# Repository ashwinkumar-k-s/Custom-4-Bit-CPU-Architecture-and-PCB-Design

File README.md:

# Custom 4-Bit CPU Architecture and PCB Design

Designed and simulated a 4-bit microprocessor datapath using discrete logic, including an ALU, program counter, and memory units. Created full schematic and PCB layouts for all individual modules using KiCad, and successfully fabricated and tested the physical ALU board.

## System Architecture

This project implements a rudimentary discrete logic 4-bit processor datapath. The architecture is modularly designed, consisting of the following key components:

### Program Counter (PC)
* 2 Bit Counter using D-Flip Flop to cycle between 4 instructions

### Instruction Memory
* A network of 8 4x1 MUXs to obtain an instruction of 8 bit wide and have 4 instructions at a time loaded.

### 4x4 Memory Unit
* Consists of 4 2x4 Decoders, 4 4-Bit Registers and 4 4x1 MUXs.
* 2x4 Decoder : Used to load values into the register, controlled using Enable signals while in write mode.
* 4-Bit Register: Receives data from Decoders, interconnected as, all Bit-0s from decoder to Register-1, all Bit-1s from decoder to Register-2, all Bit-2s from decoder to Register-3, all Bit-3s from decoder to Register-4.
* 4x1 MUX: Used to read data from the register when in read mode, similar interconnect network as instruction memory.

### Operand controller
* Complementary pair of Tri-State Buffers connected to both Registers containing operand A and B

### Arithmetic Logic Unit (ALU)
* Could do 7 operations AND, OR, XOR, ADD, SUB, ROR, ROL.
* AND, OR, XOR operations are directly computed from the received inputs directly using dedicated ICs.
* ADD and SUB is done in a single circuit consisting of 2 Full adders and a XOR IC, where ADD = A+B and SUB = A + 2's complement(B).
* Rotate operations ROR (right) and ROL (left) is done with a 4-bit barrel shifter(used to shift in a single clock cycle).

### Output Control Unit
* All the outputs are simultaneouslly calculated in the ALU,
* Each output is 4-Bit wide and is connected to a dedicated set of 4-Bit Tri-state buffers controlled using a 3x8 Decoder to output the desired value.
  <br>

---

## Tools & Technologies

* **Logic Simulation:** Cedar Logic
* **Schematic Capture & PCB Layout:** KiCad
* **Hardware:** Discrete logic ICs, custom fabricated PCB

---

## Hardware Implementation & PCB Design

All functional modules were modeled, schematized, and routed as individual PCBs. The ALU module was fabricated in PCB and the rest were validated in breadboard circuitry.

### Hardware implementation of 4x4 Memory unit 

<br>

* 4 4x1 MUXs - 74LS153.
* 4 4-Bit Registers - 74LS173.
* 4 2x4 Decoder - 74LS139.
<br>

<br>

### Hardware implementation of Memory Data Register (Operand Selector)

<br>

* 3 4-Bit Registers - 74LS173.
* 1 8xTri-State Buffers - 74LS244.
* 1x2 Decoder made using AND and NOT ICs.

### ALU implementaion in PCB

<br>

* AND - 7408.
* OR - 7432.
* XOR - 7486.
* 4-Bit Full Adder - 7483.
* 4x1 MUX - 74153.
<br>

<br>

### Output Control Unit

<br>

* 3x8 Decoder - 74138.
* 7 4-Bit Registers - 74173.
<br>

<br>

### KiCad PCB Layouts

<br>

<br>

* PCB Layout of Memory Unit
<br>

<br>

<br>

* PCB layout of ALU
<br>

<br>

<br>

* PCB layout of Output Control Unit

### Cedar Logic Simulation

<br>

---

## Repository Structure

```text
├── simulations/          # Cedar Logic simulation files
│   ├── full_layout 
├── kicad_projects/       # KiCad schematics and PCB layout files
│   ├── Output_control_unit/
│   ├── ALU_module/
│   └── 4x4_Memory_Unit/     
└── README.md
 ```

## Contributors

This 4-bit CPU architecture and PCB design project was collaboratively developed as an assigned group project. 

* **[Adithya Balesh (CB.EN.U4ECE23005)/adithyabalesh]** - *Digital Design and Hardware Verification and PCB*
  * Instruction Memory and Component Integration and verification.
  * Hardware Implementation of Output control unit and ALU.
  * PCB routing and layout arrangement of memory.
  * Poster and Documentation.

* **[Ashwin Kumar K S (CB.EN.U4ECE23007)/ashwinkumar-k-s]** - *ALU Design and PCB routing,hardware impllementaion*
  * ALU, Output Control Unit and Datapath design.
  * Component Selection and Hardware implementation of ALU and Memory data register.
  * PCB routing, layout, and schematic generation of ALU and Output control Unit 
  * Documentation and Github Repo Creation.
  
* **[Chokkalingam S (CB.EN.U4ECE23012)/-------]** - *Memory Design and hardware impllementaion*
  * Digital design of 4x4 Memory Unit,  Memory Data Register Design and Pipeline/Interconnects accross all modules.
  * Hardware implementation and verification of Memory module and Instruction Memory.
  * PCB schematic of Memory module.
  * Documentation.

* **[Rohith J (CB.EN.U4ECE23017)/-------]** - *Digital Design and Hardware Verification*
  * Digital design verification of all components.
  * Hardware circuit implementation of and Memory Units.
  * PCB schematic verification and soldering.
  * Poster, Presentation and Documentation

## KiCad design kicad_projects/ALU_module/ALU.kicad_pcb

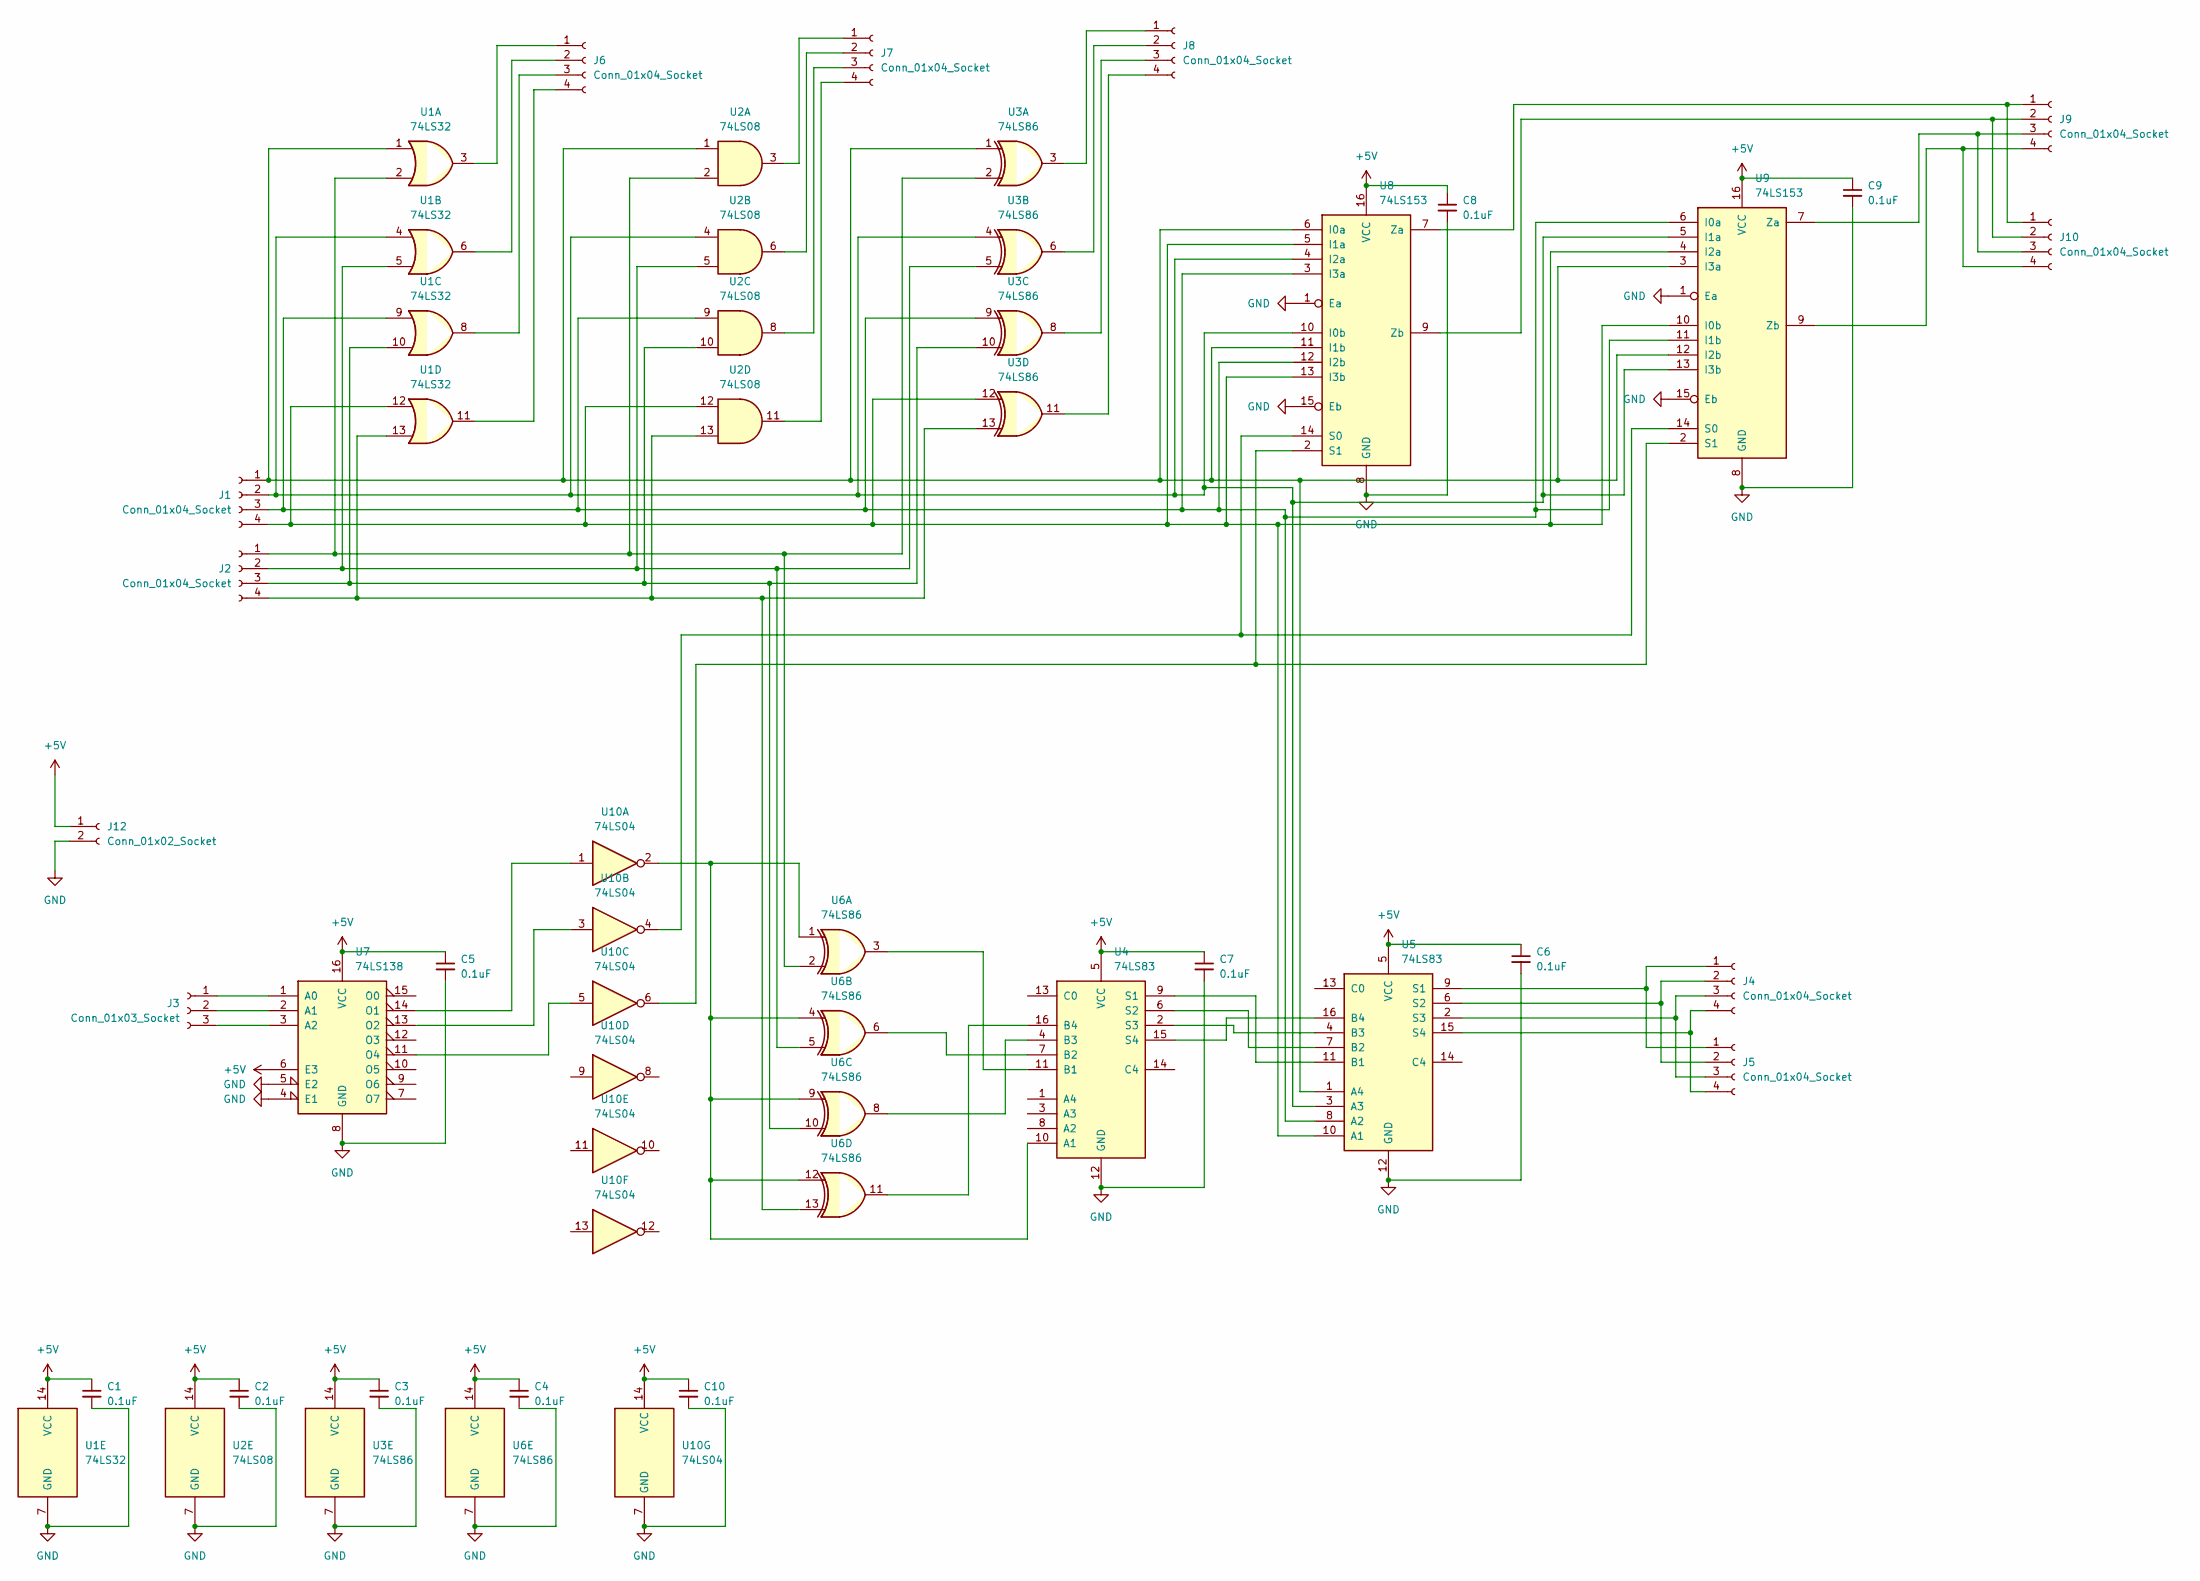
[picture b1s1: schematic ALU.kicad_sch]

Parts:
C1, C2, C3, C4, C5, C6, C7, C8, C9, C10: 0.1uF; C_Disc_D5.0mm_W2.5mm_P2.50mm
J1, J2, J4, J5, J6, J7, J8, J9, J10: Conn_01x04_Socket; PinSocket_1x04_P2.54mm_Vertical
J3: Conn_01x03_Socket; PinSocket_1x03_P2.54mm_Vertical
J12: Conn_01x02_Socket; PinSocket_1x02_P2.54mm_Vertical
U1: 74LS32; DIP-14_W7.62mm_LongPads
U2: 74LS08; DIP-14_W7.62mm_LongPads
U3, U6: 74LS86; DIP-14_W7.62mm_LongPads
U4, U5: 74LS83; DIP-16_W7.62mm_LongPads
U7: 74LS138; DIP-16_W7.62mm_LongPads
U8, U9: 74LS153; DIP-16_W7.62mm_LongPads
U10: 74LS04; DIP-14_W7.62mm_LongPads

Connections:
+5V: C1.1, C2.1, C3.1, C4.1, C5.1, C6.1, C7.1, C8.1, C9.1, C10.1, J12.1, U1.14 (VCC), U2.14 (VCC), U3.14 (VCC), U4.5 (VCC), U5.5 (VCC), U6.14 (VCC), U7.6 (E3), U7.16 (VCC), U8.16 (VCC), U9.16 (VCC), U10.14 (VCC)
GND: C1.2, C2.2, C3.2, C4.2, C5.2, C6.2, C7.2, C8.2, C9.2, C10.2, J12.2, U1.7 (GND), U2.7 (GND), U3.7 (GND), U4.12 (GND), U5.12 (GND), U6.7 (GND), U7.4 (E1), U7.5 (E2), U7.8 (GND), U8.1 (Ea), U8.8 (GND), U8.15 (Eb), U9.1 (Ea), U9.8 (GND), U9.15 (Eb), U10.7 (GND)
unnamed: J1.1, U1.1, U2.1, U3.1, U5.1 (A4), U8.6 (I0a), U8.11 (I1b), U9.3 (I3a), U9.12 (I2b)
unnamed: J1.2, U1.4, U2.4, U3.4, U5.3 (A3), U8.4 (I2a), U8.10 (I0b), U9.5 (I1a), U9.13 (I3b)
unnamed: J1.3, U1.9, U2.9, U3.9, U5.8 (A2), U8.3 (I3a), U8.12 (I2b), U9.6 (I0a), U9.11 (I1b)
unnamed: J1.4, U1.12, U2.12, U3.12, U5.10 (A1), U8.5 (I1a), U8.13 (I3b), U9.4 (I2a), U9.10 (I0b)
unnamed: J2.1, U1.2, U2.2, U3.2, U6.2
unnamed: J2.2, U1.5, U2.5, U3.5, U6.5
unnamed: J2.3, U1.10, U2.10, U3.10, U6.10
unnamed: J2.4, U1.13, U2.13, U3.13, U6.13
unnamed: J3.1, U7.1 (A0)
unnamed: J3.2, U7.2 (A1)
unnamed: J3.3, U7.3 (A2)
unnamed: J4.1, J5.1, U5.9 (S1)
unnamed: J4.2, J5.2, U5.6 (S2)
unnamed: J4.3, J5.3, U5.2 (S3)
unnamed: J4.4, J5.4, U5.15 (S4)
unnamed: J6.1, U1.3
unnamed: J6.2, U1.6
unnamed: J6.3, U1.8
unnamed: J6.4, U1.11
unnamed: J7.1, U2.3
unnamed: J7.2, U2.6
unnamed: J7.3, U2.8
unnamed: J7.4, U2.11
unnamed: J8.1, U3.3
unnamed: J8.2, U3.6
unnamed: J8.3, U3.8
unnamed: J8.4, U3.11
unnamed: J9.1, J10.1, U8.7 (Za)
unnamed: J9.2, J10.2, U8.9 (Zb)
unnamed: J9.3, J10.3, U9.7 (Za)
unnamed: J9.4, J10.4, U9.9 (Zb)
unnamed: U4.10 (A1), U6.1, U6.4, U6.9, U6.12, U10.2
unnamed: U4.11 (B1), U6.3
unnamed: U4.7 (B2), U6.6
unnamed: U4.4 (B3), U6.8
unnamed: U4.16 (B4), U6.11
unnamed: U4.9 (S1), U5.11 (B1)
unnamed: U4.6 (S2), U5.7 (B2)
unnamed: U4.2 (S3), U5.4 (B3)
unnamed: U4.15 (S4), U5.16 (B4)
unnamed: U7.14 (O1), U10.1
unnamed: U7.13 (O2), U10.3
unnamed: U7.11 (O4), U10.5
unnamed: U8.14 (S0), U9.14 (S0), U10.4
unnamed: U8.2 (S1), U9.2 (S1), U10.6

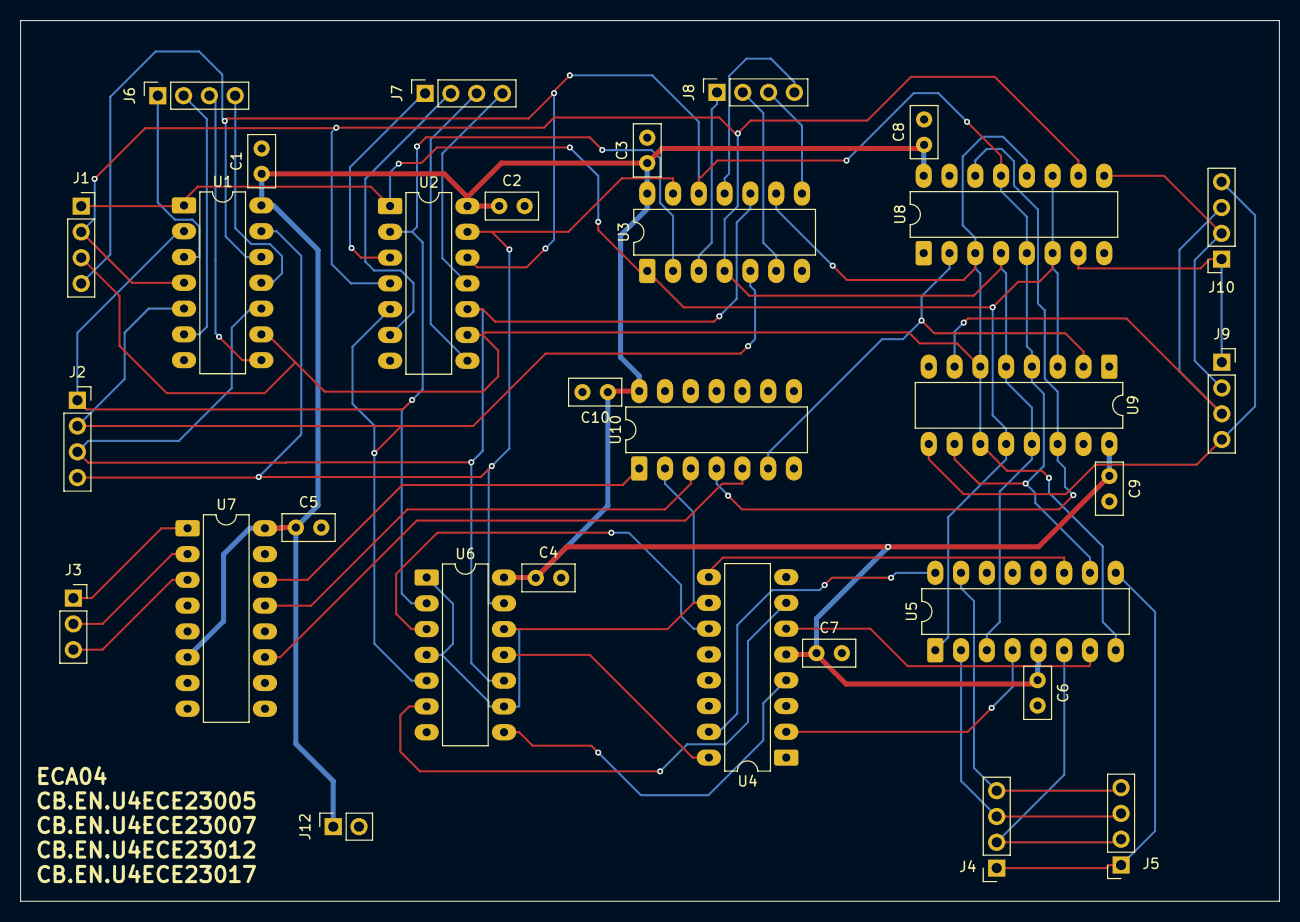
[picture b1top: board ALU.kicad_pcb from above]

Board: 2 copper layers, 124.0 x 86.8 mm, 31 parts (0 on the bottom side), 47 nets.

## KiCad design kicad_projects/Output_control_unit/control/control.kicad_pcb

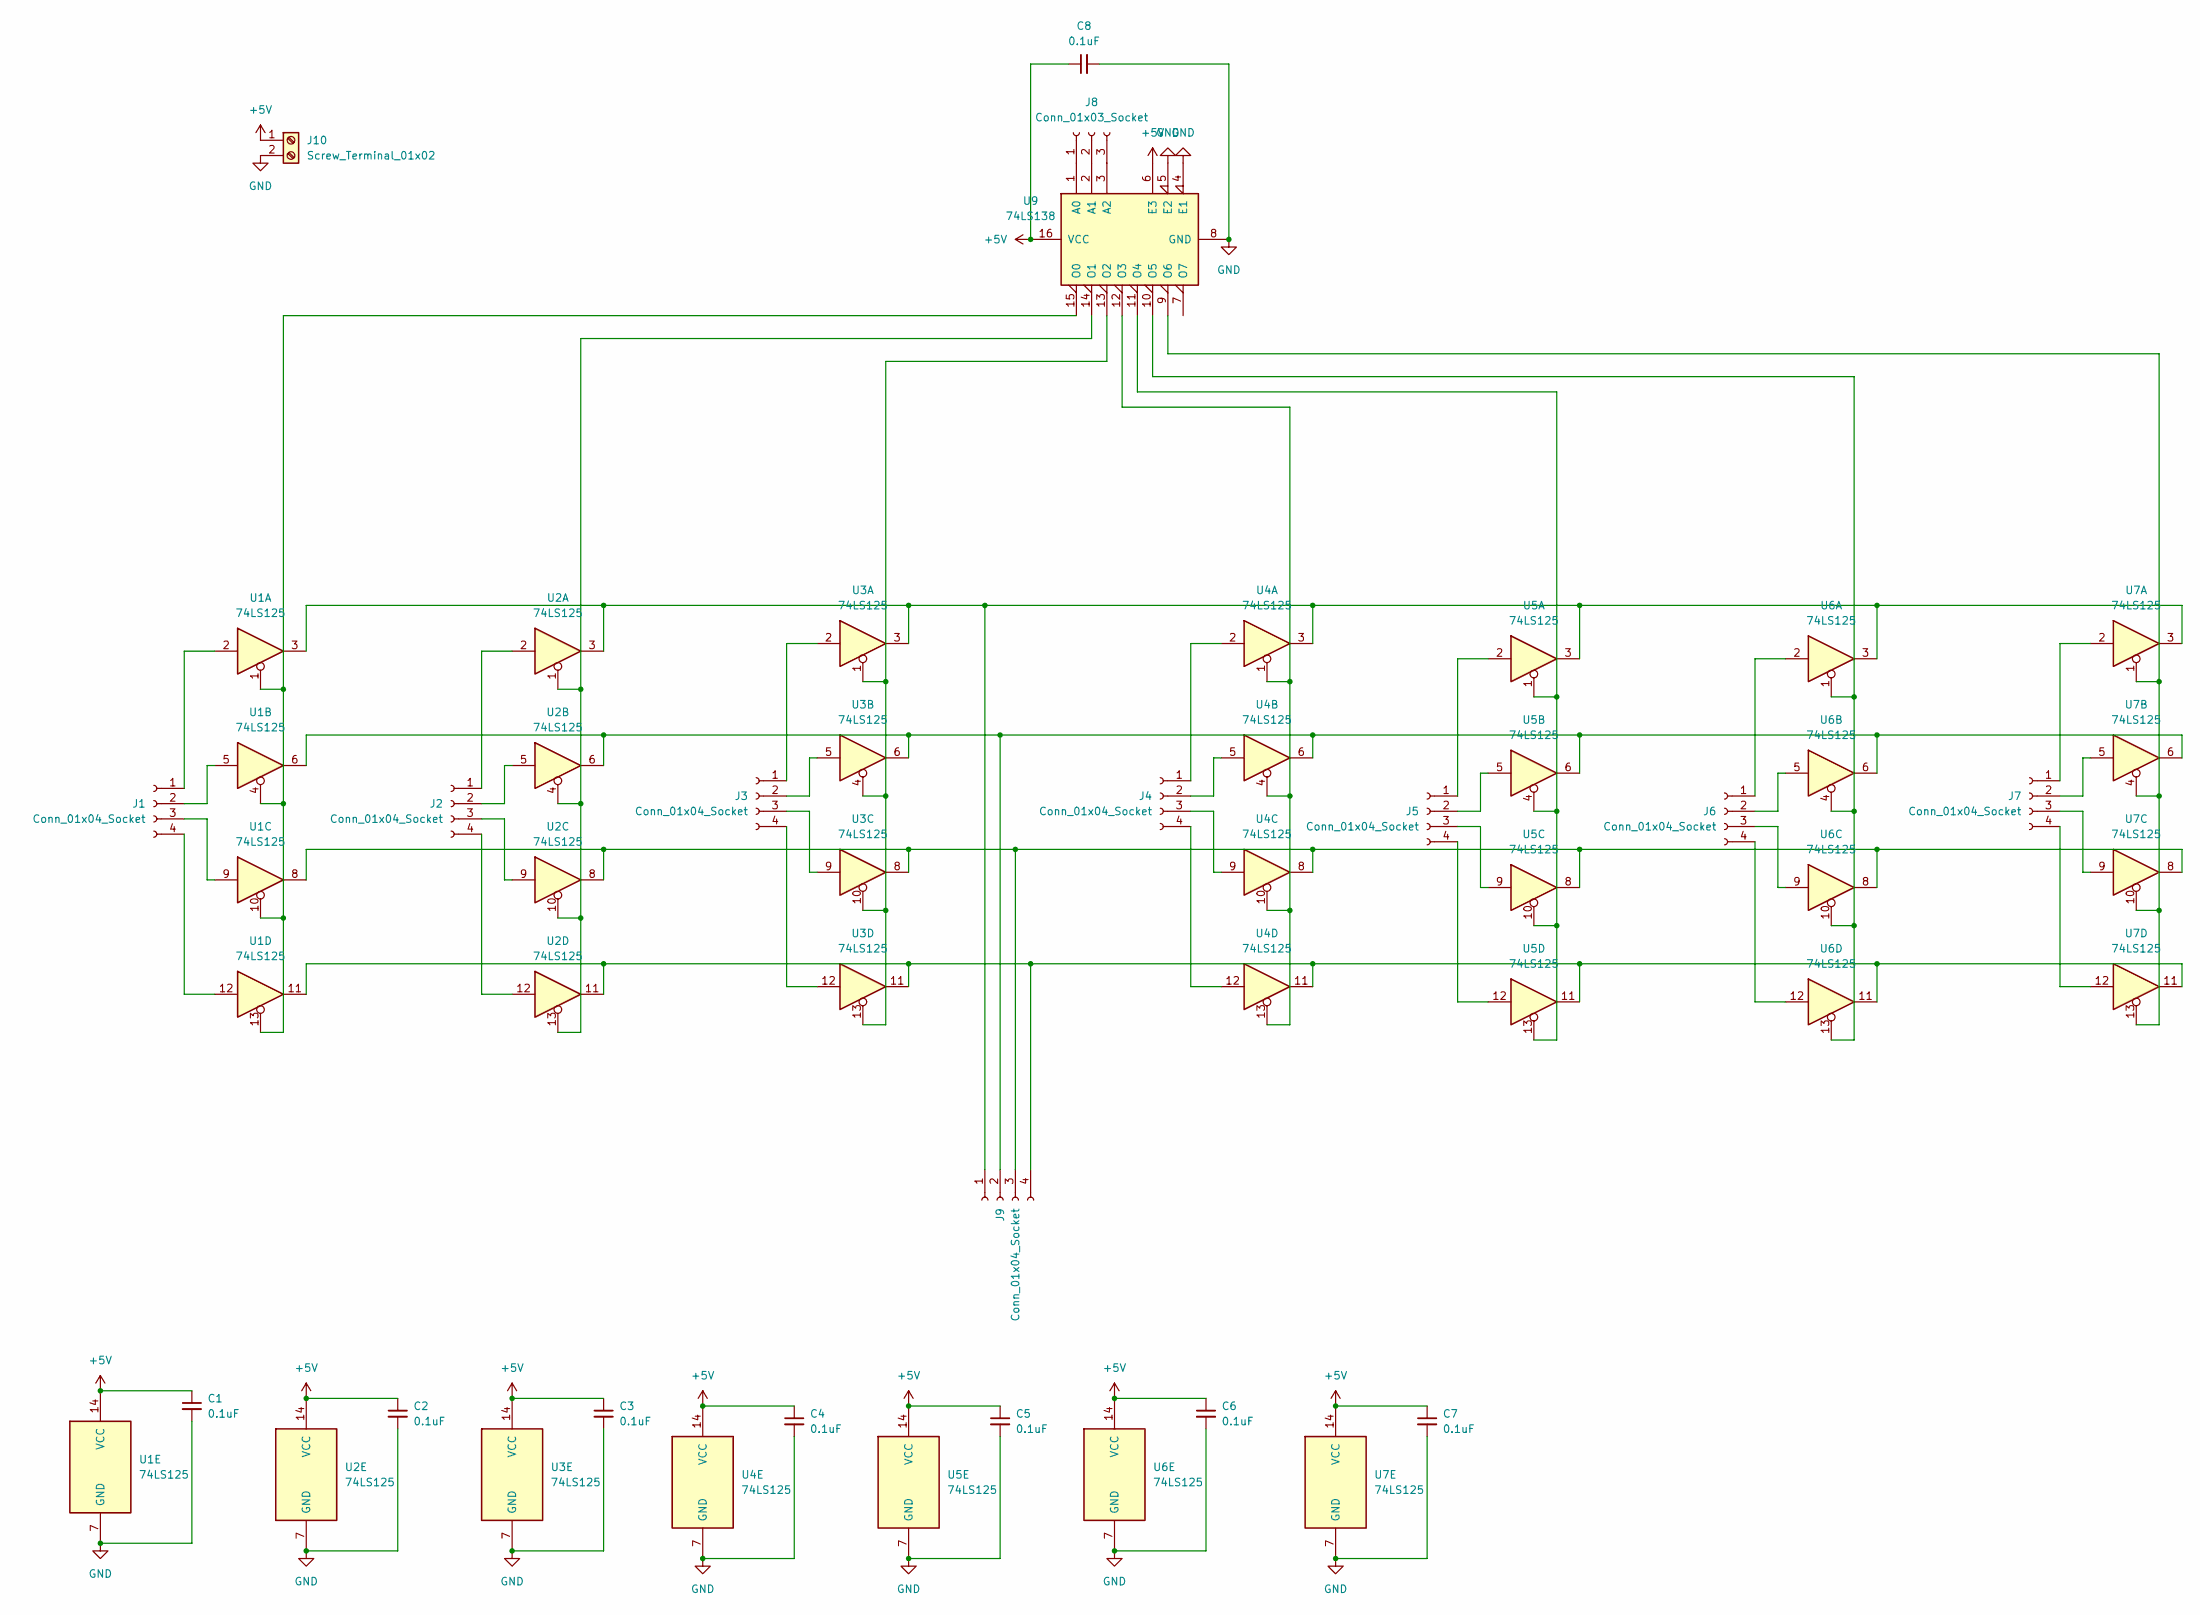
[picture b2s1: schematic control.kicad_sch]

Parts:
C1, C2, C3, C4, C5, C6, C7, C8: 0.1uF; C_Disc_D5.0mm_W2.5mm_P2.50mm
J1, J2, J3, J4, J5, J6, J7, J9: Conn_01x04_Socket; PinSocket_1x04_P2.54mm_Vertical
J8: Conn_01x03_Socket; PinSocket_1x03_P2.54mm_Vertical
J10: Screw_Terminal_01x02; TerminalBlock_MetzConnect_Type094_RT03502HBLU_1x02_P5.00mm_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
U1, U2, U3, U4, U5, U6, U7: 74LS125; DIP-14_W7.62mm_LongPads
U9: 74LS138; DIP-16_W7.62mm_LongPads

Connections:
+5V: C1.1, C2.1, C3.1, C4.1, C5.1, C6.1, C7.1, C8.1, J10.1, U1.14 (VCC), U2.14 (VCC), U3.14 (VCC), U4.14 (VCC), U5.14 (VCC), U6.14 (VCC), U7.14 (VCC), U9.6 (E3), U9.16 (VCC)
GND: C1.2, C2.2, C3.2, C4.2, C5.2, C6.2, C7.2, C8.2, J10.2, U1.7 (GND), U2.7 (GND), U3.7 (GND), U4.7 (GND), U5.7 (GND), U6.7 (GND), U7.7 (GND), U9.4 (E1), U9.5 (E2), U9.8 (GND)
unnamed: J1.1, U1.2
unnamed: J1.2, U1.5
unnamed: J1.3, U1.9
unnamed: J1.4, U1.12
unnamed: J2.1, U2.2
unnamed: J2.2, U2.5
unnamed: J2.3, U2.9
unnamed: J2.4, U2.12
unnamed: J3.1, U3.2
unnamed: J3.2, U3.5
unnamed: J3.3, U3.9
unnamed: J3.4, U3.12
unnamed: J4.1, U4.2
unnamed: J4.2, U4.5
unnamed: J4.3, U4.9
unnamed: J4.4, U4.12
unnamed: J5.1, U5.2
unnamed: J5.2, U5.5
unnamed: J5.3, U5.9
unnamed: J5.4, U5.12
unnamed: J6.1, U6.2
unnamed: J6.2, U6.5
unnamed: J6.3, U6.9
unnamed: J6.4, U6.12
unnamed: J7.1, U7.2
unnamed: J7.2, U7.5
unnamed: J7.3, U7.9
unnamed: J7.4, U7.12
unnamed: J8.1, U9.1 (A0)
unnamed: J8.2, U9.2 (A1)
unnamed: J8.3, U9.3 (A2)
unnamed: J9.1, U1.3, U2.3, U3.3, U4.3, U5.3, U6.3, U7.3
unnamed: J9.2, U1.6, U2.6, U3.6, U4.6, U5.6, U6.6, U7.6
unnamed: J9.3, U1.8, U2.8, U3.8, U4.8, U5.8, U6.8, U7.8
unnamed: J9.4, U1.11, U2.11, U3.11, U4.11, U5.11, U6.11, U7.11
unnamed: U1.1, U1.4, U1.10, U1.13, U9.15 (O0)
unnamed: U2.1, U2.4, U2.10, U2.13, U9.14 (O1)
unnamed: U3.1, U3.4, U3.10, U3.13, U9.13 (O2)
unnamed: U4.1, U4.4, U4.10, U4.13, U9.12 (O3)
unnamed: U5.1, U5.4, U5.10, U5.13, U9.11 (O4)
unnamed: U6.1, U6.4, U6.10, U6.13, U9.10 (O5)
unnamed: U7.1, U7.4, U7.10, U7.13, U9.9 (O6)

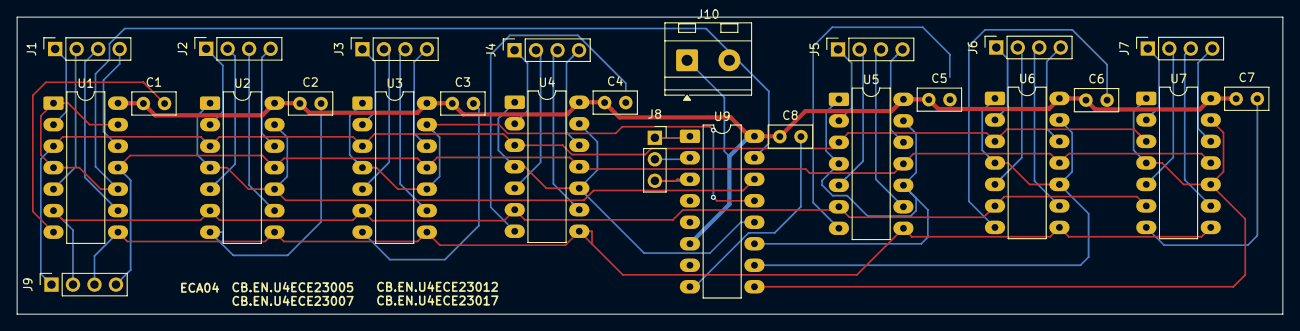
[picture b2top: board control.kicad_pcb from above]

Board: 2 copper layers, 149.6 x 35.1 mm, 26 parts (0 on the bottom side), 44 nets.

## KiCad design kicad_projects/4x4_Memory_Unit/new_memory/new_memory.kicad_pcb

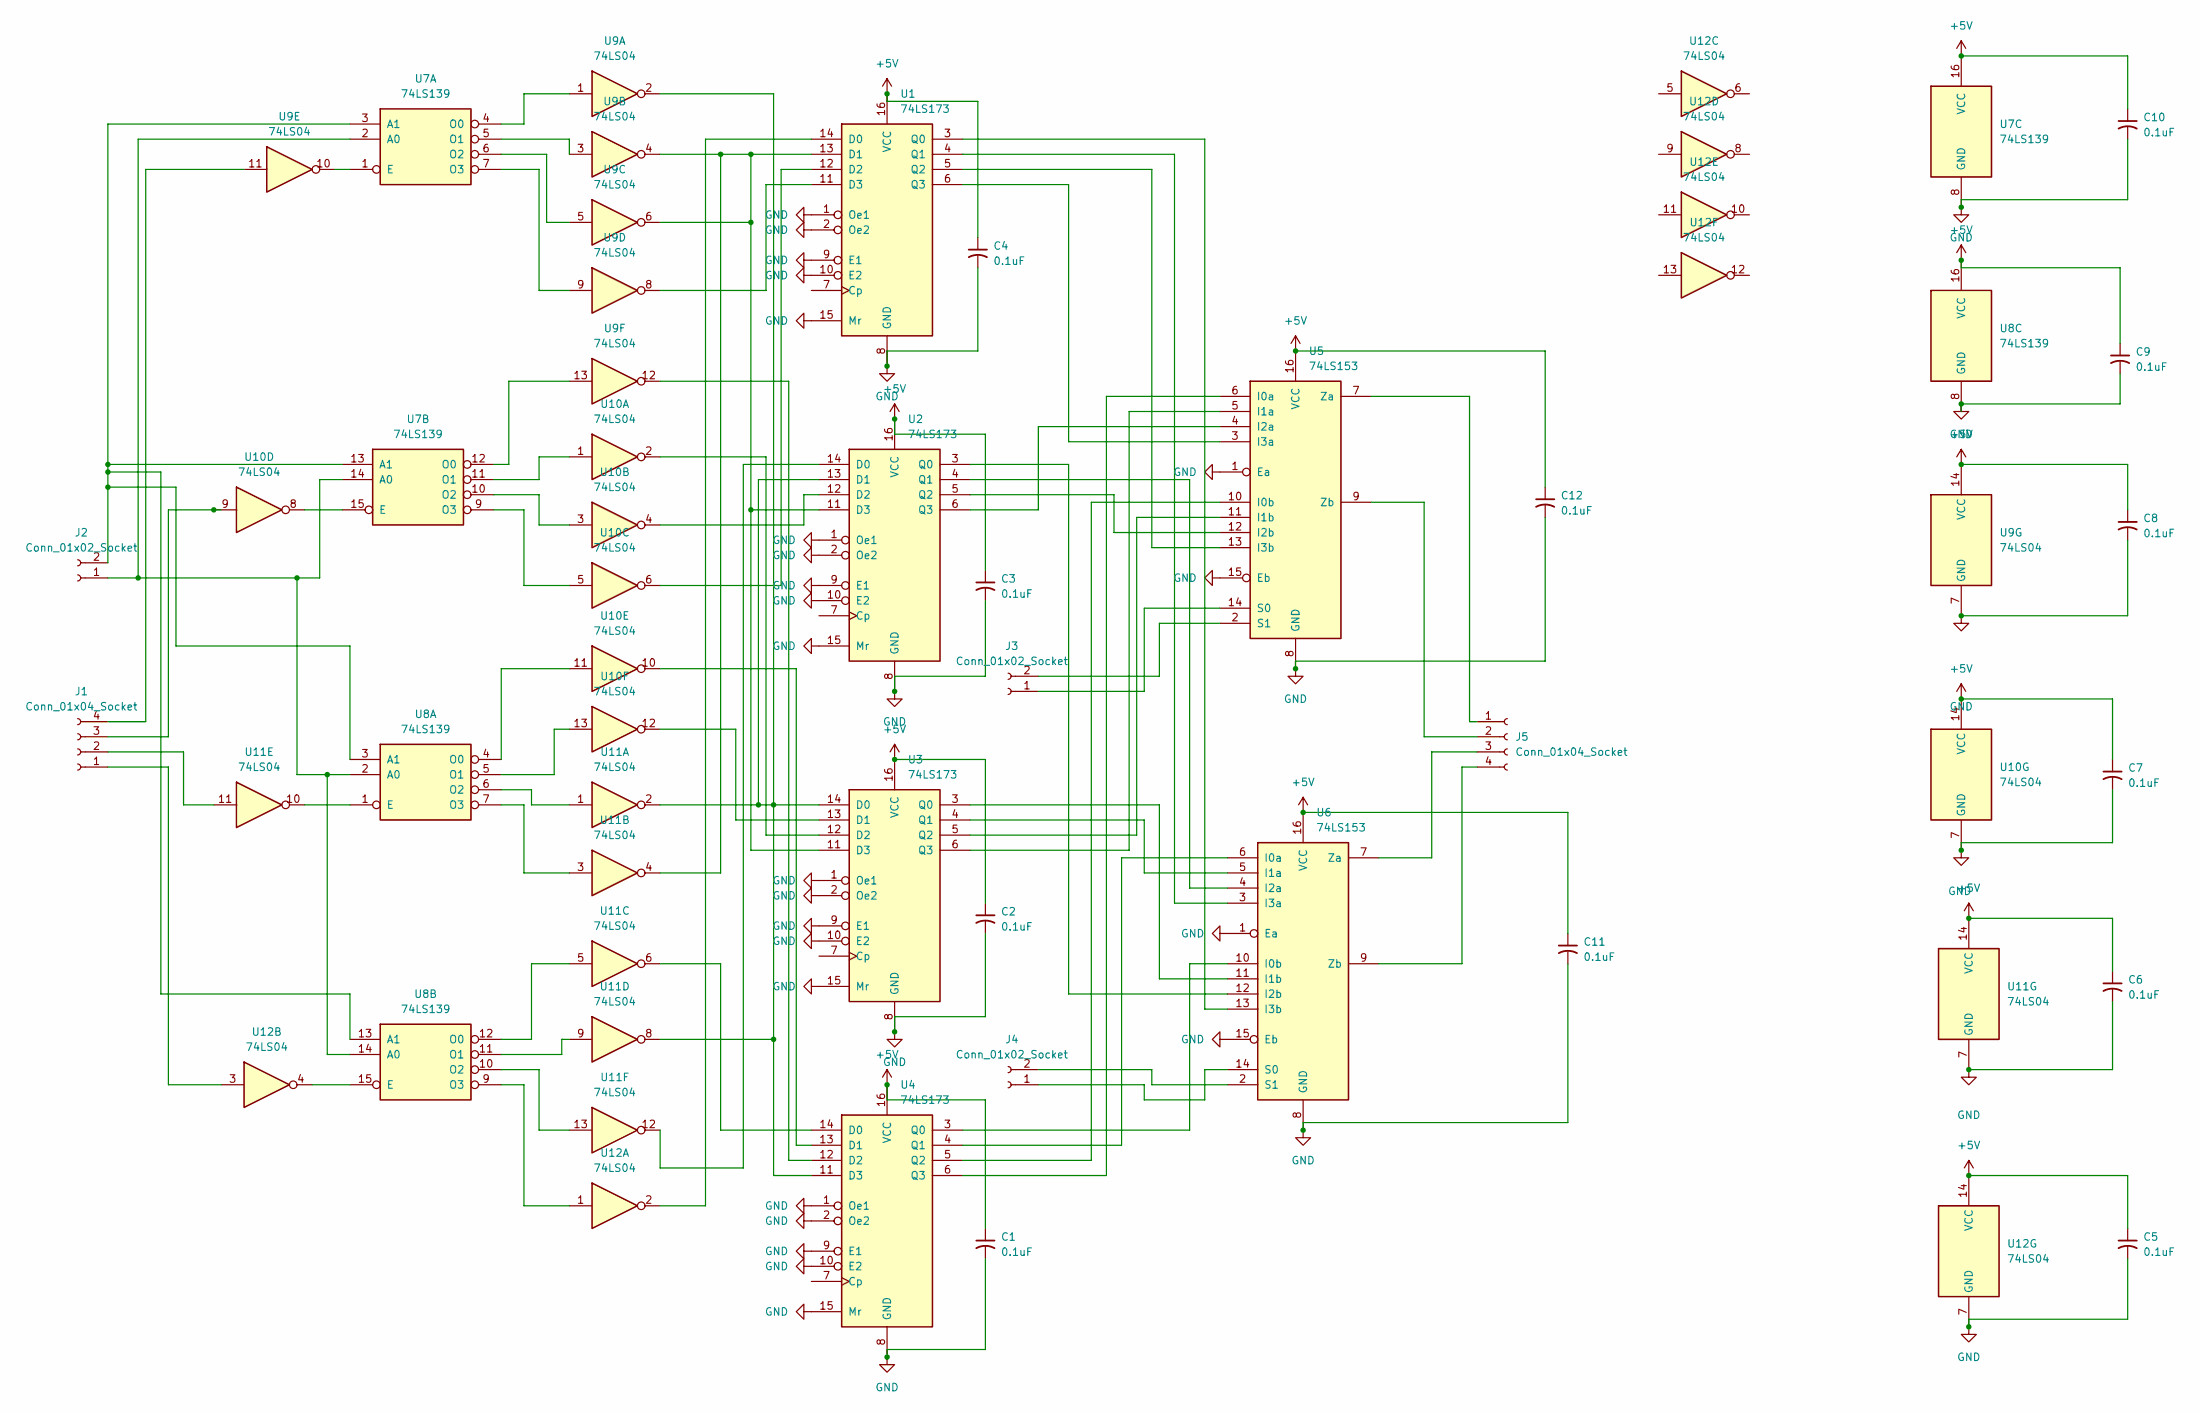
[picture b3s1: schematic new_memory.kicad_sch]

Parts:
C1, C2, C3, C4, C5, C6, C7, C8, C9, C10, C11, C12: 0.1uF; C_Disc_D5.0mm_W2.5mm_P2.50mm
J1: Conn_01x04_Socket; PinSocket_1x04_P2.54mm_Vertical
J2, J3, J4: Conn_01x02_Socket; PinSocket_1x02_P2.54mm_Vertical
J5: Conn_01x04_Socket
U1, U2, U3, U4: 74LS173; DIP-16_W7.62mm_LongPads
U5, U6: 74LS153; DIP-16_W7.62mm_LongPads
U7, U8: 74LS139; DIP-16_W7.62mm_LongPads
U9, U10, U11, U12: 74LS04; DIP-14_W7.62mm_LongPads

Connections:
+5V: C1.1, C2.1, C3.1, C4.1, C5.1, C6.1, C7.1, C8.1, C9.1, C10.1, C11.1, C12.1, U1.16 (VCC), U2.16 (VCC), U3.16 (VCC), U4.16 (VCC), U5.16 (VCC), U6.16 (VCC), U7.16 (VCC), U8.16 (VCC), U9.14 (VCC), U10.14 (VCC), U11.14 (VCC), U12.14 (VCC)
GND: C1.2, C2.2, C3.2, C4.2, C5.2, C6.2, C7.2, C8.2, C9.2, C10.2, C11.2, C12.2, U1.1 (Oe1), U1.2 (Oe2), U1.8 (GND), U1.9 (E1), U1.10 (E2), U1.15 (Mr), U2.1 (Oe1), U2.2 (Oe2), U2.8 (GND), U2.9 (E1), U2.10 (E2), U2.15 (Mr), U3.1 (Oe1), U3.2 (Oe2), U3.8 (GND), U3.9 (E1), U3.10 (E2), U3.15 (Mr), U4.1 (Oe1), U4.2 (Oe2), U4.8 (GND), U4.9 (E1), U4.10 (E2), U4.15 (Mr), U5.1 (Ea), U5.8 (GND), U5.15 (Eb), U6.1 (Ea), U6.8 (GND), U6.15 (Eb), U7.8 (GND), U8.8 (GND), U9.7 (GND), U10.7 (GND), U11.7 (GND), U12.7 (GND)
unnamed: J1.1, U12.3
unnamed: J1.2, U11.11
unnamed: J1.3, U10.9
unnamed: J1.4, U9.11
unnamed: J2.1, U7.2 (A0), U7.14 (A0), U8.2 (A0), U8.14 (A0)
unnamed: J2.2, U7.3 (A1), U7.13 (A1), U8.3 (A1), U8.13 (A1)
unnamed: J3.1, U5.14 (S0)
unnamed: J3.2, U5.2 (S1)
unnamed: J4.1, U6.14 (S0)
unnamed: J4.2, U6.2 (S1)
unnamed: J5.1, U5.7 (Za)
unnamed: J5.2, U5.9 (Zb)
unnamed: J5.3, U6.7 (Za)
unnamed: J5.4, U6.9 (Zb)
unnamed: U1.14 (D0), U12.2
unnamed: U1.13 (D1), U2.11 (D3), U3.11 (D3), U9.4, U9.6, U11.4
unnamed: U1.12 (D2), U10.6
unnamed: U1.11 (D3), U9.8
unnamed: U1.3 (Q0), U6.13 (I3b)
unnamed: U1.4 (Q1), U6.3 (I3a)
unnamed: U1.5 (Q2), U5.13 (I3b)
unnamed: U1.6 (Q3), U5.3 (I3a)
unnamed: U2.14 (D0), U11.12
unnamed: U2.13 (D1), U3.14 (D0), U4.11 (D3), U9.2, U11.2, U11.8
unnamed: U2.12 (D2), U10.4
unnamed: U2.3 (Q0), U6.12 (I2b)
unnamed: U2.4 (Q1), U6.4 (I2a)
unnamed: U2.5 (Q2), U5.12 (I2b)
unnamed: U2.6 (Q3), U5.4 (I2a)
unnamed: U3.13 (D1), U10.12
unnamed: U3.12 (D2), U10.2
unnamed: U3.3 (Q0), U6.11 (I1b)
unnamed: U3.4 (Q1), U6.5 (I1a)
unnamed: U3.5 (Q2), U5.11 (I1b)
unnamed: U3.6 (Q3), U5.5 (I1a)
unnamed: U4.14 (D0), U11.6
unnamed: U4.13 (D1), U10.10
unnamed: U4.12 (D2), U9.12
unnamed: U4.3 (Q0), U6.10 (I0b)
unnamed: U4.4 (Q1), U6.6 (I0a)
unnamed: U4.5 (Q2), U5.10 (I0b)
unnamed: U4.6 (Q3), U5.6 (I0a)
unnamed: U7.1 (E), U9.10
unnamed: U7.4 (O0), U9.1
unnamed: U7.5 (O1), U9.3
unnamed: U7.6 (O2), U9.5
unnamed: U7.7 (O3), U9.9
unnamed: U7.15 (E), U10.8
unnamed: U7.12 (O0), U9.13
unnamed: U7.11 (O1), U10.1
unnamed: U7.10 (O2), U10.3
unnamed: U7.9 (O3), U10.5
unnamed: U8.1 (E), U11.10
unnamed: U8.4 (O0), U10.11
unnamed: U8.5 (O1), U10.13
unnamed: U8.6 (O2), U11.1
unnamed: U8.7 (O3), U11.3
unnamed: U8.15 (E), U12.4
unnamed: U8.12 (O0), U11.5
unnamed: U8.11 (O1), U11.9
unnamed: U8.10 (O2), U11.13
unnamed: U8.9 (O3), U12.1

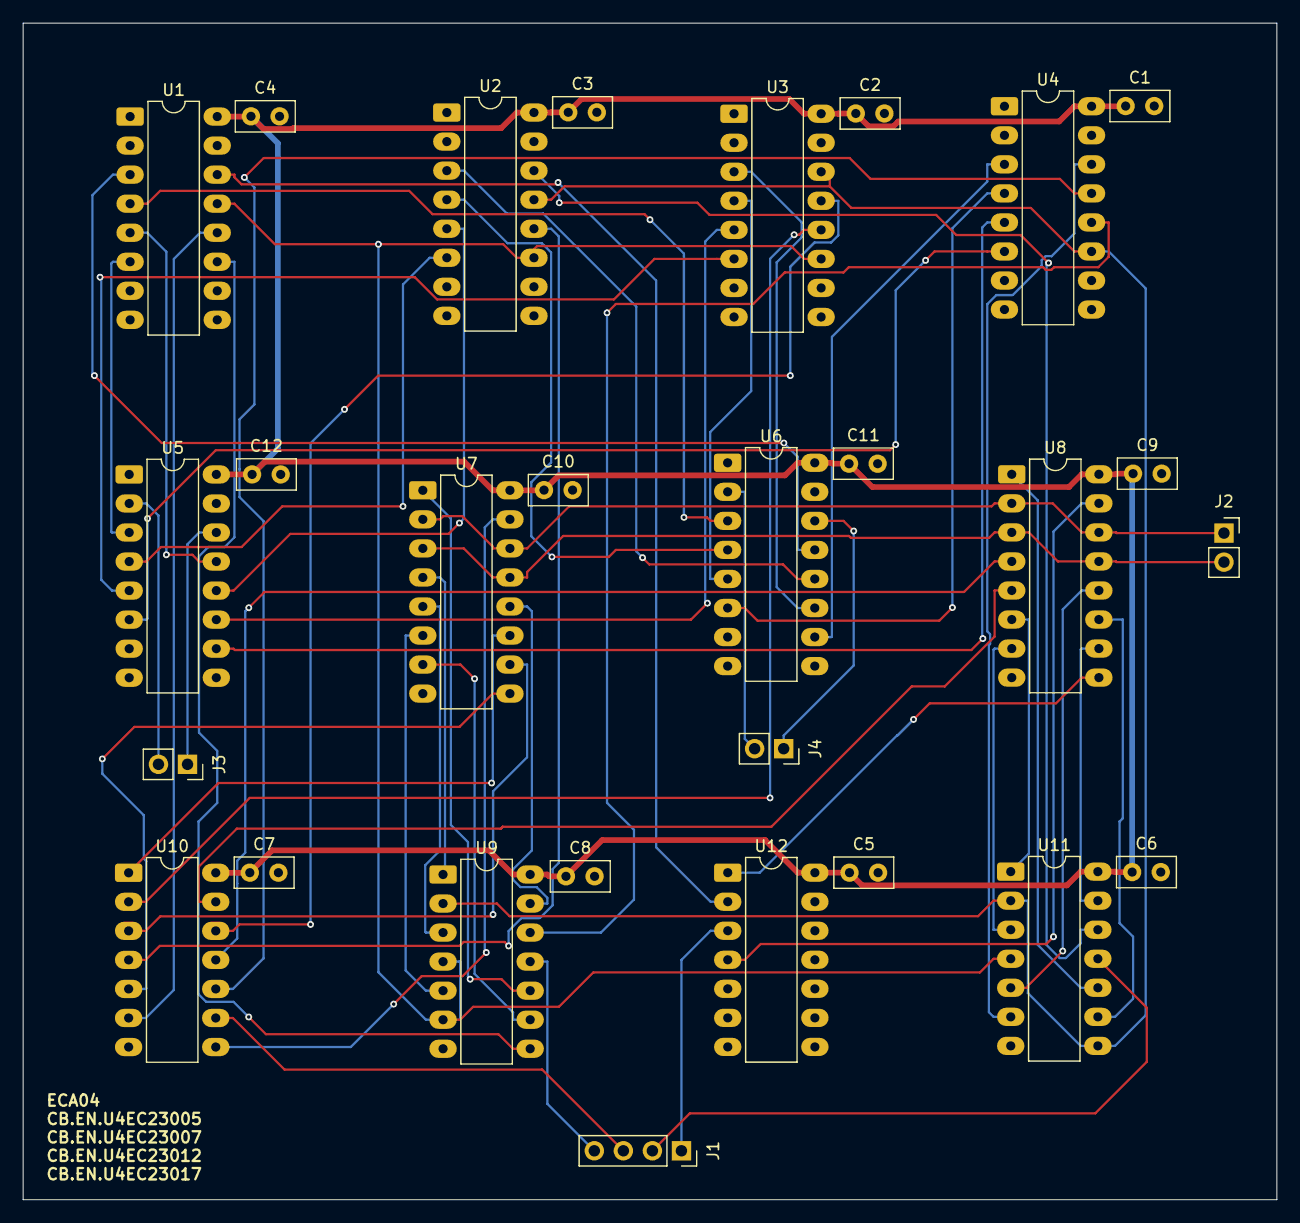
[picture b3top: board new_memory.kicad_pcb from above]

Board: 2 copper layers, 109.7 x 102.9 mm, 28 parts (0 on the bottom side), 60 nets.
